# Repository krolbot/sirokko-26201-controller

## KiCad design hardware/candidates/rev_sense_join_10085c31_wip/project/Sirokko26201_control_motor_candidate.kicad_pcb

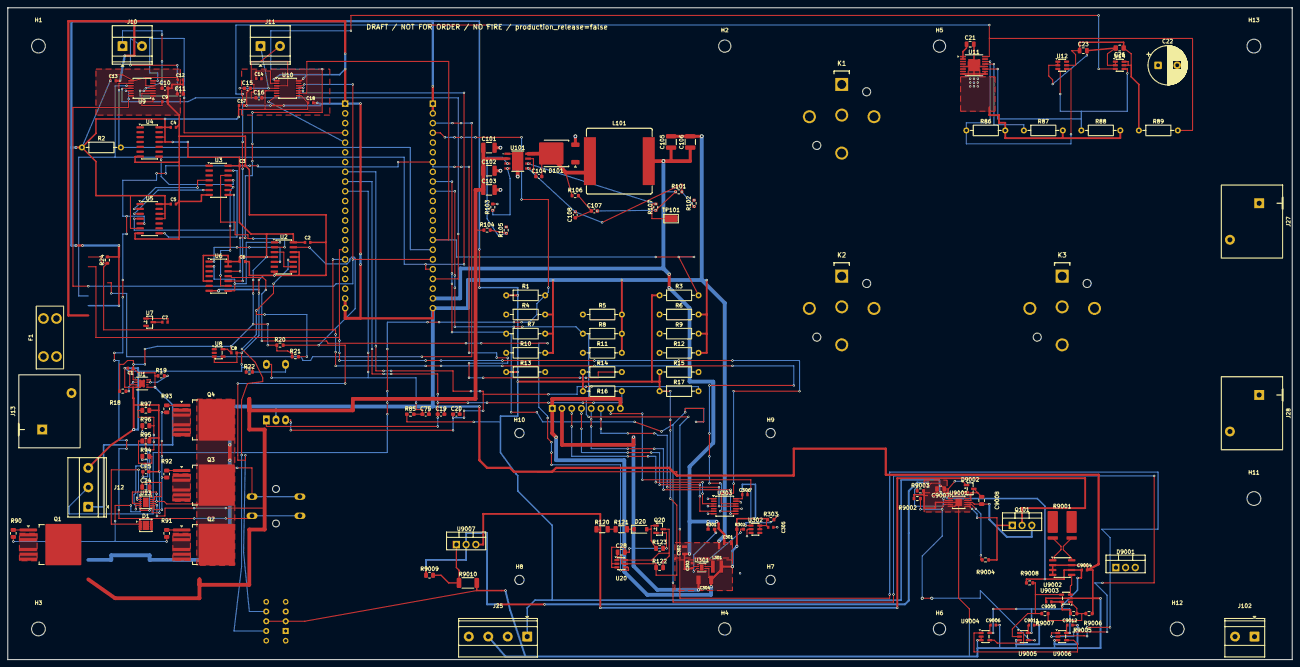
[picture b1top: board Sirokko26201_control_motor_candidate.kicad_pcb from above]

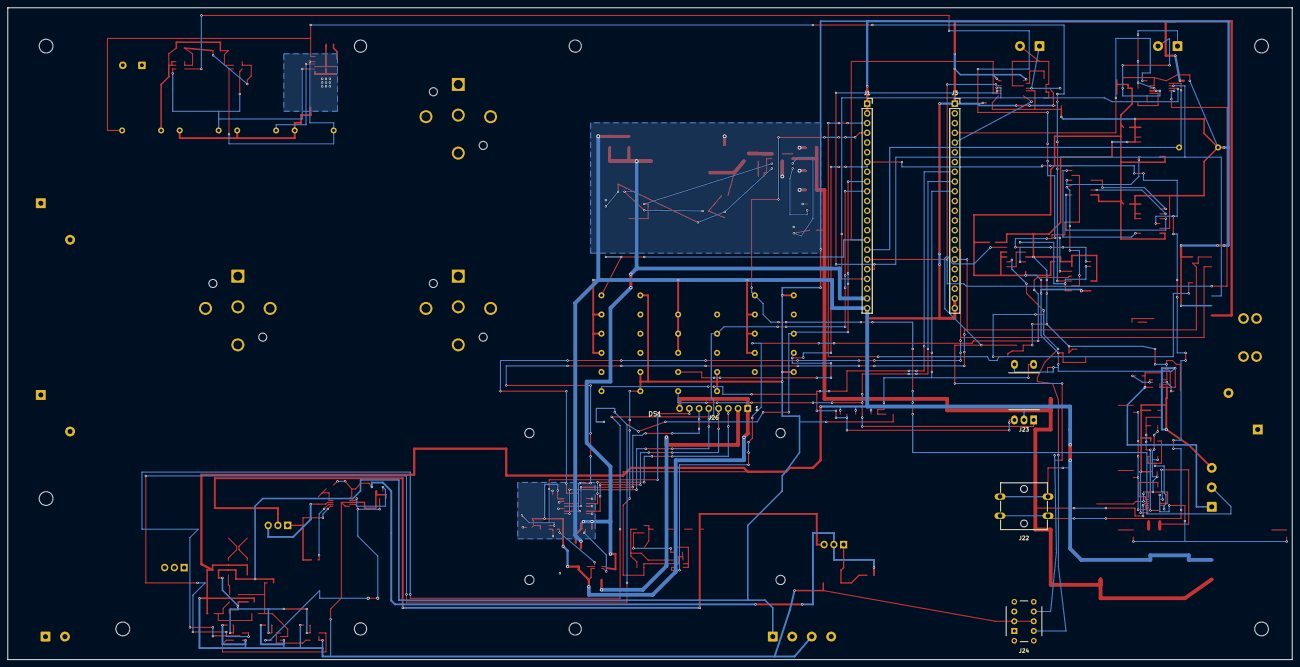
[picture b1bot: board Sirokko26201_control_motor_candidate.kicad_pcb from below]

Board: 2 copper layers, 335.0 x 170.0 mm, 181 parts (7 on the bottom side), 110 nets.

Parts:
C1, C2, C3, C4, C5, C6, C7, C8: 100n 16V X7R; C_Murata_GRM188_1608_Reflow
C9, C14: 0.1uF X7R 16V BIAS; C_Murata_GRM188_1608_Reflow
C10, C15: 0.01uF X7R 16V T+ filter; C_0603_1608Metric
C11, C16: 0.01uF X7R 16V T- filter; C_0603_1608Metric
C12, C17: 0.1uF X7R 16V AVDD; C_Murata_GRM188_1608_Reflow
C13, C18: 0.1uF X7R 16V DVDD; C_Murata_GRM188_1608_Reflow
C19: 10n ENC_A_FILTER; C_0603_1608Metric_Pad1.08x0.95mm_HandSolder
C20: 10n ENC_B_FILTER; C_0603_1608Metric_Pad1.08x0.95mm_HandSolder
C21: 100nF 100V X7R GRM21BR72A104KAC4L VM_BYPASS; C_0805_2012Metric
C22: 330uF 63V EEUFS1J331L BULK_DRAFT; CP_Radial_D10.0mm_P5.00mm
C23: 100nF 50V X7R U12_BYPASS; C_0805_2012Metric
C24: 220nF 100V CVCAP GRM21BR72A224KA01L; C_0805_2012Metric
C25: 100nF 100V CVS GRM188R72A104KA35D; C_0603_1608Metric
C26: 100nF 50V X7R U14_BYPASS; C_0805_2012Metric_Pad1.18x1.45mm_HandSolder
C28: 100nF 100V X7R 10% GRM21BR72A104KAC4L; C_0805_2012Metric
C75: 10n; C_0603_1608Metric_Pad1.08x0.95mm_HandSolder
C101, C102: 2.2uF 100V X7R; C_1210_3225Metric
C103: 22uF 100V BULK; C_1210_3225Metric
C104: 2.2nF 50V X7R; C_0603_1608Metric
C105, C106: 47uF 16V X7R; C_1210_3225Metric
C107: 4.7nF 50V C0G; C_0603_1608Metric
C108: 820pF 50V C0G; C_0603_1608Metric
C301, C302: 10uF GRM21BR61E106KA73L; C_Murata_GRM21B_2012_Reflow
C303: 100nF GRM188R71E104KA01D; C_Murata_GRM188_1608_Reflow
C304: 47uF GRM32ER61C476KE15L; C_Murata_GRM32E_3225_Reflow
C305, C306: 100nF; C_Murata_GRM188_1608_Reflow
C9004, C9005, C9006: 100nF X7R 16V; C_Murata_GRM188_1608_Reflow
C9007: 1uF ±10% X7R 50V 0805; LTC7001 VCC local decoupli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; C_0805_2012Metric
C9008: 1uF ±10% X7R 50V 0805 (BST-TS); C_0805_2012Metric
C9011: 100nF X7R 16V 10%; U9005 local bypass; C_Murata_GRM188_1608_Reflow
C9012: 100nF X7R 16V 10%; U9006 local bypass; C_Murata_GRM188_1608_Reflow
D1: TVS3301DRBR WIP; VSON-8-1EP_3x3mm_P0.65mm_EP1.65x2.4mm
D20: BZT52C15-7-F 15V 500mW; D_SOD-123
D101: STPS5H100B-TR; TO-252-2
D9001: STPS30H100CW; common cathode: K/pin2/tab -> MOTOR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; TO-220-3_Vertical
D9002: MMBD1501A; 200V 200mA silicon low-leakage bootstr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; SOT-23
DS1: Waveshare 18366 / 2.4inch LCD Module; Waveshare_18366_Module_Bside_Envelope_NO_CY
F1: 0997030.WXN / 30A WIP; Keystone_3568_MINI_Blade_3D_ENVELOPE
H1, H3, H11, H12, H13: MountingHole_3.6mm_R5.5_DRAFT
H2, H4: M3; MountingHole_3.2mm_M3
H5, H6: M3 SUPPORT; MountingHole_3.2mm_M3
H7, H8, H9, H10: WAVESHARE18366_M2_DRAFT_NOT_FOR_ORDER; MountingHole_2.4mm_M2_DRAFT
J1: DEVKITC1_J1; PinSocket_1x22_P2.54mm_Vertical
J3: DEVKITC1_J3; PinSocket_1x22_P2.54mm_Vertical
J10: TC_K_EXHAUST_T+_T-; TerminalBlock_Phoenix_MKDS-1,5-2-5.08_1x02_P5.08mm_Horizont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
J11: TC_K_AIR_T+_T-; TerminalBlock_Phoenix_MKDS-1,5-2-5.08_1x02_P5.08mm_Horizont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
J12: ROOM_DS18B20_HARNESS; TerminalBlock_Phoenix_MKDS-1,5-3-5.08_1x03_P5.08mm_Horizont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
J13: 24V_INPUT_PHOENIX_1756993_WIP; Phoenix_1756993_MKDS5HV_2_9.52_ZSZS_3D_ENVELOPE
J22: START_STOP B3F-4055 + B32-1380 RED; SW_SPST_Omron_B3F-40xx
J23: ENCODER EC11E15244G1 + KNOB 41001-1; RotaryEncoder_Alps_EC11E15244G1_Knob41001_3D_ENVELOPE
J24: RESET NKK BB25AB-FA; SW_NKK_BB25AB-FA_3D_ENVELOPE
J25: THERMAL_AND_HW_ENABLE_3V3_ONLY; TerminalBlock_Phoenix_MKDS-1,5-4-5.08_1x04_P5.08mm_Horizont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
J26: TFT CABLE HARWIN M20-9960845 RA THT; Harwin_M20_9960845_1x08_P2.54mm_RA_THT_Bside
J27: GLOW_OUTPUT_PHOENIX_1756993; Phoenix_1756993_MKDS5HV_2_9.52_ZSZS_3D_ENVELOPE
J28: CLUTCH_OUTPUT_PHOENIX_1756993; Phoenix_1756993_MKDS5HV_2_9.52_ZSZS_3D_ENVELOPE
J102: MOTOR_24V_HIGH_SPEED; 125W_HEATER_NAMEPLATE_NOT_M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; TerminalBlock_Phoenix_MKDS-1,5-2-5.08_1x02_P5.08mm_Horizont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
K1: DG85BM-5021-76-1024 + DZ85AB-5-PCB / GLOW; DZ85AB_5_PCB_DG85BM_ENVELOPE
K2: DG85BM-5021-76-1024 + DZ85AB-5-PCB / CLUTCH_RUN; DZ85AB_5_PCB_DG85BM_ENVELOPE
K3: DG85BM-5021-76-1024 + DZ85AB-5-PCB / CLUTCH_SAFE; DZ85AB_5_PCB_DG85BM_ENVELOPE
L101: 33uH Isat>=10A; L_Bourns_SRP1770TA_16.9x16.9mm
L301: 744025003 3.3uH; L_Wuerth_744025003_2828_Reflow
Q1, Q2, Q3, Q4: IPB017N10N5LFATMA1 WIP; Infineon_PG_TO263_7_IPB017N10N5LF
Q20: BC847B,215; SOT-23
Q101: IRFB4110PBF (100V; RDS(on) @ VGS=10V); TO-220-3_Vertical
R1: 4k7; R_Axial_DIN0207_L6.3mm_D2.5mm_P10.16mm_Horizontal
R2, R3, R4, R5, R6, R7, R8, R9, R10, R11, R12, R13, R14, R15: 10k; R_Axial_DIN0207_L6.3mm_D2.5mm_P10.16mm_Horizontal
R16: 2.2k ENC_A_PULLUP; R_Axial_DIN0207_L6.3mm_D2.5mm_P10.16mm_Horizontal
R17: 2.2k ENC_B_PULLUP; R_Axial_DIN0207_L6.3mm_D2.5mm_P10.16mm_Horizontal
R18, R19, R20, R21, R22, R102, R105, R107: 10k 1%; R_0603_1608Metric
R24: 10k TFT_CS_PULLUP; R_0603_1608Metric
R85: 2.2k; R_0603_1608Metric_Pad0.98x0.95mm_HandSolder
R86: 4k7 DRV_IN1_PULLDOWN; R_Axial_DIN0207_L6.3mm_D2.5mm_P10.16mm_Horizontal
R87: 4k7 DRV_IN2_PULLDOWN; R_Axial_DIN0207_L6.3mm_D2.5mm_P10.16mm_Horizontal
R88: 4k7 DRV_IN3_PULLDOWN; R_Axial_DIN0207_L6.3mm_D2.5mm_P10.16mm_Horizontal
R89: 10k RELAY_DRIVER_OK_PULLUP; R_Axial_DIN0207_L6.3mm_D2.5mm_P10.16mm_Horizontal
R90: 4.7R Q1_GATE; R_0805_2012Metric
R91: 4.7R Q2_GATE; R_0805_2012Metric
R92: 4.7R Q3_GATE; R_0805_2012Metric
R93: 4.7R Q4_GATE; R_0805_2012Metric
R94: 84.5k 1% OV_TOP; R_0805_2012Metric
R95: 3.48k 1% OV_BOT; R_0805_2012Metric
R96: 75k 1% EN_TOP; R_0805_2012Metric
R97: 5.62k 1% EN_BOT; R_0805_2012Metric
R101, R103: 31.6k 1%; R_0603_1608Metric
R104: 100k 1%; R_0603_1608Metric
R106: 82k 1%; R_0603_1608Metric
R120, R121: 2.7k 1% 0.25W RC1206FR-072K7L; R_1206_3216Metric
R122: 47k 1% 0.125W RC0805FR-0747KL; R_0805_2012Metric
R123: 100k 1% 0.125W RC0805FR-07100KL; R_0805_2012Metric
R301: 100k 1% EN; R_Yageo_RC0603_1608_Reflow
R302: 100k 1% PG; R_Yageo_RC0603_1608_Reflow
R303: 100k; R_0603_1608Metric
R9001: WSLP27262L000FEA; 2mOhm 1% 5W @70C; WSLP2726
R9002: 100k 1% gate-command pull-down; R_0603_1608Metric
R9003: 130k 1% (VCCUV ≈9.1V rising); R_0603_1608Metric
R9004: 10R gate turn-on damping; R_0603_1608Metric
R9005: 30.1k 1% OCP threshold high; R_0603_1608Metric
R9006: 10.0k 1% OCP threshold low; R_0603_1608Metric
R9007: 1.00M 1% OCP hysteresis feedback; R_0603_1608Metric
R9008: 10k 1% OCP_OK pull-up; R_0603_1608Metric
R9009: 75R 1% 0.125W; LM317 OUT→ADJ; R_0805_2012Metric
R9010: 681R 1% 0.75W; LM317 ADJ→GND; R_2010_5025Metric
TP101: PGOOD_5V_NOT_GPIO; TestPoint_Keystone_5015_Micro_Mini
U1: TPS3431SDRBR; TPS3431_DRB0008A_3D
U2: SN74HCS74D; SOIC-14_3.9x8.7mm_P1.27mm
U3: SN74HCS14D; SOIC-14_3.9x8.7mm_P1.27mm
U4, U5: SN74HCS30D; SOIC-14_3.9x8.7mm_P1.27mm
U6: SN74HCS11D; SOIC-14_3.9x8.7mm_P1.27mm
U7: TPS3839G33DBZR; SOT-23
U8: SN74LVC1G14DBVR; SOT-23-5
U9, U10: MAX31856MUD+; TSSOP-14_4.4x5mm_P0.65mm
U11: DRV8803PWPR; HTSSOP-16-1EP_4.4x5mm_P0.65mm_EP3x3mm
U12, U14, U20: SN74LVC1G97DBVR; SOT-23-6
U13: LM74800QDRRRQ1 WIP_NOT_TRANSIENT_QUALIFIED; WSON-12-1EP_3x3mm_P0.5mm_EP1.5x2.5mm
U101: LM5013DDAR; DDA0008B_LM5013DDAR_TI4214849B_3D
U301: TPS62162DSGR; Texas_DSG0008A_WSON-8-1EP_2x2mm_P0.5mm_EP0.9x1.6mm
U302: TPS3808G33DBVR; SOT-23-6
U303: 74LVC125APW,118 Nexperia ONLY; TSSOP-14_4.4x5mm_P0.65mm
U9001: LTC7001IMSE#PBF; MSOP-10 EP; MSOP-10-1EP_3x3mm_P0.5mm_EP1.68x1.88mm
U9002: INA240A1ID; SOIC-8_3.9x4.9mm_P1.27mm
U9003: TLV9020DBVR; SOT-23-5
U9004: SN74LVC1G32DBVR; SOT-23-5
U9005, U9006: SN74LVC1G08DBVR; SOT-23-5
U9007: LM317HVT/NOPB TO-220; TJ 0…125C; TO-220-3_Vertical

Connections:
+5V_DEVKIT: C105.1, C106.1, C107.2, C301.1, C302.1, C303.1, J1.21, L101.2, R101.1, R107.1, R301.1, U301.2
/+3V3: C1.1, C2.1, C3.1, C4.1, C5.1, C6.1, C7.1, C8.1, C12.1, C13.1, C17.1, C18.1, C23.1, C26.1, C28.1, C9004.1, C9005.1, C9006.1, C9011.1, C9012.1, J1.1, J1.2, J12.1, J25.1, R1.1, R2.1, R3.1, R13.1, R14.1, R15.1, R16.1, R17.1, R18.1, R19.1, R20.1, R21.1, R24.2, R85.1, R89.1, R122.1, R9005.1, R9008.1, U1.1, U1.3, U1.5, U2.4, U2.14, U3.14, U4.11, U4.12, U4.14, U5.6, U5.11, U5.12, U5.14, U6.5, U6.13, U6.14, U7.3, U8.5, U9.5, U9.8, U10.5, U10.8, U12.5, U14.5, U14.6, U20.1, U20.5, U9002.6, U9003.5, U9004.5, U9005.5, U9006.5
/ALLOW_LATCH: U2.5, U6.1
/ARM_READY: J3.7, R10.1, U4.5, U5.1
/CLEAR_OK: U2.1, U6.2, U6.8
/CLEAR_OK_BASE: U3.10, U6.9
/CLUTCH_STAGE1: K2.87, K3.30
/CLUTCH_SWITCHED_POS: J28.1, K3.87
/ENC_A: C19.1, J3.9, J23.1, R16.2
/ENC_B: C20.1, J3.8, J23.3, R17.2
/ENC_SW: C75.1, J3.10, J23.4, R85.2
/EXT_SAFETY_ENABLE: J25.4, U6.6
/FAN_REQUEST: J1.9, R7.1, U9006.1
/FUEL_CMD: J1.8, R5.1, R87.1, U3.3, U11.13
/FUEL_PERMIT: J3.18, R6.1, U3.5, U6.4
/GLOW_CMD: J1.20, R4.1, U3.9, U12.6
/GLOW_ENABLE_HW: R86.1, U11.14, U12.4
/GLOW_SWITCHED_POS: J27.1, K1.87
/GND: C1.2, C2.2, C3.2, C4.2, C5.2, C6.2, C7.2, C8.2, C9.2, C10.2, C11.2, C12.2, C13.2, C14.2, C15.2, C16.2, C17.2, C18.2, C19.2, C20.2, C21.2, C22.2, C23.2, C25.2, C26.2, C28.2, C75.2, C101.2, C102.2, C103.2, C105.2, C106.2, C301.2, C302.2, C303.2, C304.2, C305.2, C306.2, C9004.2, C9005.2, C9006.2, C9007.2, C9011.2, C9012.2, D1.5, D1.6, D1.7, D1.8, D101.3, D9001.1, D9001.3, J1.22, J3.1, J3.21, J3.22, J12.3, J13.2, J22.2, J23.2, J23.5, J24.2, J24.5, J25.3, J26.2, J27.2, J28.2, J102.2, Q20.2, R4.2, R5.2, R6.2, R7.2, R8.2, R9.2, R10.2, R11.2, R12.2, R22.2, R86.2, R87.2, R88.2, R95.2, R97.2, R102.2, R103.2, R105.2, R123.2, R9002.2, R9003.2, R9006.2, R9010.2, U1.4, U1.9, U2.7, U2.11, U2.12, U3.7, U4.7, U5.7, U6.7, U7.1, U8.3, U9.1, U9.14, U10.1, U10.14, U11.5, U11.8, U11.9, U11.10, U11.12, U11.17, U12.1, U12.2, U13.7, U14.1, U14.2, U20.2, U20.3, U101.1, U101.9, U301.1, U301.4, U301.5, U301.9, U302.2, U303.1, U303.4, U303.7, U303.10, U303.13, U9001.3, U9001.5, U9001.11, U9002.2, U9002.3, U9002.4, U9002.7, U9003.2, U9004.2, U9004.3, U9005.3, U9006.3
/HW_RESET_CLK: U2.3, U2.9
/INPUT_PROTECTION_WIP_NOT_QUALIFIED/CAP_NET: C24.1, U13.11
/INPUT_PROTECTION_WIP_NOT_QUALIFIED/DGATE: R90.1, R91.1, U13.1
/INPUT_PROTECTION_WIP_NOT_QUALIFIED/EN_DIV: R96.2, R97.1, U13.6
/INPUT_PROTECTION_WIP_NOT_QUALIFIED/HGATE: R92.1, R93.1, U13.8
/INPUT_PROTECTION_WIP_NOT_QUALIFIED/OV_DIV: R94.2, R95.1, U13.5
/INPUT_PROTECTION_WIP_NOT_QUALIFIED/Q1_GATE: Q1.1, R90.2
/INPUT_PROTECTION_WIP_NOT_QUALIFIED/Q2_GATE: Q2.1, R91.2
/INPUT_PROTECTION_WIP_NOT_QUALIFIED/Q3_GATE: Q3.1, R92.2
/INPUT_PROTECTION_WIP_NOT_QUALIFIED/Q4_GATE: Q4.1, R93.2
/INPUT_PROTECTION_WIP_NOT_QUALIFIED/REV_MID: C24.2, C25.1, Q1.4, Q2.4, Q3.4, Q4.4, R94.1, R96.1, U13.3, U13.4, U13.10, U13.12
/INPUT_PROTECTION_WIP_NOT_QUALIFIED/VIN_FUSED: D1.1, D1.2, D1.3, D1.4, F1.2, Q1.2, Q1.3, Q1.5, Q1.6, Q1.7, Q2.2, Q2.3, Q2.5, Q2.6, Q2.7, U13.2
/K_CLUTCH_RUN_COIL_LOW: K2.85, U11.4
/K_CLUTCH_SAFE_COIL_LOW: K3.85, U11.6
/K_GLOW_COIL_LOW: K1.85, U11.3
/LOGIC_POWER_24_TO_5V__DRAFT_NOT_FOR_ORDER/BOOT: C104.1, U101.7
/LOGIC_POWER_24_TO_5V__DRAFT_NOT_FOR_ORDER/EN_LOGIC: R104.2, R105.1, U101.3
/LOGIC_POWER_24_TO_5V__DRAFT_NOT_FOR_ORDER/FB: C108.2, R101.2, R102.1, U101.5
/LOGIC_POWER_24_TO_5V__DRAFT_NOT_FOR_ORDER/PGOOD_5V: R107.2, TP101.1, U101.6
/LOGIC_POWER_24_TO_5V__DRAFT_NOT_FOR_ORDER/RAMP: C107.1, C108.1, R106.2
/LOGIC_POWER_24_TO_5V__DRAFT_NOT_FOR_ORDER/RON: R103.1, U101.4
/LOGIC_POWER_24_TO_5V__DRAFT_NOT_FOR_ORDER/SW: C104.2, D101.2, L101.1, R106.1, U101.8
/MOTOR_PWM_REBUILD_CANDIDATE/BST: C9008.1, D9002.3, U9001.9
/MOTOR_PWM_REBUILD_CANDIDATE/FAN_REQUEST_OR_EMERG: U9004.4, U9005.1
/MOTOR_PWM_REBUILD_CANDIDATE/FAN_WORK_PWM: U9004.1, U9006.4
/MOTOR_PWM_REBUILD_CANDIDATE/GATE_Q101: Q101.1, R9004.2, U9001.6
/MOTOR_PWM_REBUILD_CANDIDATE/ISENSE_OUT: U9002.5, U9003.3
/MOTOR_PWM_REBUILD_CANDIDATE/MOTOR_GATE_CMD: R9002.1, U9001.4, U9005.4
/MOTOR_PWM_REBUILD_CANDIDATE/MOTOR_POS: D9001.2, J102.1, R9001.2, U9002.1
/MOTOR_PWM_REBUILD_CANDIDATE/OCP_OK: R9007.1, R9008.2, U9003.4, U9005.2
/MOTOR_PWM_REBUILD_CANDIDATE/OCP_THRESH: R9005.2, R9006.1, R9007.2, U9003.1
/MOTOR_PWM_REBUILD_CANDIDATE/SW_SHUNT_HI: C9008.2, Q101.3, R9001.1, U9001.8, U9002.8
/MOTOR_PWM_REBUILD_CANDIDATE/TGUP: R9004.1, U9001.7
/MOTOR_PWM_REBUILD_CANDIDATE/VADJ: R9009.2, R9010.1, U9007.1
/MOTOR_PWM_REBUILD_CANDIDATE/VCCUV: R9003.1, U9001.2
/MOTOR_PWM_REBUILD_CANDIDATE/VDRV12V: C9007.1, D9002.1, R9009.1, U9001.1, U9007.2
/NOT_CLEAR_OK: U3.11, U4.8
/NOT_FUEL_CMD: U3.4, U5.2
/NOT_FUEL_PERMIT: U3.6, U5.3
/NOT_GLOW_CMD: U3.8, U5.4
/NOT_RESET_ACCEPT: U3.13, U5.8
/NOT_SW_TRIP: U3.2, U4.6
/P24_BASE: D20.2, Q20.1, R123.1
/P24_PRESENT: U6.11, U20.4
/P24_PROTECTED: C21.1, C22.1, C101.1, C102.1, C103.1, K1.30, K1.86, K2.30, K2.86, K3.86, Q3.2, Q3.3, Q3.5, Q3.6, Q3.7, Q4.2, Q4.3, Q4.5, Q4.6, Q4.7, Q101.2, R104.1, R120.1, U11.1, U11.2, U13.9, U101.2, U9007.3
/P24_SENSE_N: Q20.3, R122.2, U20.6
/P24_SERIES_MID: R120.2, R121.1
/P24_ZENER_K: D20.1, R121.2
/PG_OK: U4.1, U7.2
/RELAY_DRIVER_OK: R89.2, U6.10, U11.16
/RESET_ACCEPT: U2.2, U3.12
/RESET_HW_NC_N: J24.6, R20.2, U2.13
/RESET_HW_NO_N: J24.4, R21.2, U2.10
/RESET_REQUEST: J1.6, J24.1, R13.2
/ROOM_DQ: J1.4, J12.2, R1.2
/SAFETY_OK: J1.5, R12.1, R88.1, U6.3, U11.11, U12.3, U14.4
/SAFETY_OK_RAW: U6.12, U14.3
/SPEED_CMD: J1.10, R8.1, U9006.2
/START_REQUEST: J1.7, J22.1, R14.2, U5.5
/STOP_OK: U4.3, U8.4
/STOP_STATUS: J1.12, R15.2, U8.2
/SW_TRIP: J3.6, R11.1, U3.1
/TC_AIR_BIAS: C14.1, U10.2
/TC_AIR_CS: J1.15, R3.2, U10.9
/TC_AIR_DRDY: J3.5, U10.7
/TC_AIR_TM: C16.1, J11.2, U10.3
/TC_AIR_TP: C15.1, J11.1, U10.4
/TC_EXH_BIAS: C9.1, U9.2
/TC_EXH_CS: J1.16, R2.2, U9.9
/TC_EXH_DRDY: J3.4, U9.7
/TC_EXH_TM: C11.1, J10.2, U9.3
/TC_EXH_TP: C10.1, J10.1, U9.4
/TC_SCK: J1.18, U9.10, U10.10, U303.5
/TC_SDI_MOSI: J1.17, U9.12, U10.12, U303.2
/TC_SDO_MISO: J1.19, U9.11, U10.11
/TFT_3V3: C304.1, C305.1, C306.1, J26.1, J26.8, L301.2, R302.1, R303.1, U301.6, U302.5, U302.6, U303.14
/TFT_CS: J3.17, R24.1, U303.9
/TFT_CS_BUF: J26.5, U303.8
/TFT_DC: J3.16, U303.12
/TFT_DC_BUF: J26.6, U303.11
/TFT_MOSI_BUF: J26.3, U303.3
/TFT_POWER_3V3_DRAFT/TFT_3V3_PG: R302.2, U301.8
/TFT_POWER_3V3_DRAFT/TFT_PWR_EN: R301.2, U301.3
/TFT_POWER_3V3_DRAFT/TFT_PWR_SW: L301.1, U301.7
/TFT_RESET_N: J26.7, R303.2, U302.1
/TFT_SCK_BUF: J26.4, U303.6
/THERMAL_OK: J25.2, R22.1, U4.4
/VIN_RAW_24: F1.1, J13.1
/WD_CWD_FIXED: R18.2, U1.2
/WD_HEARTBEAT: J1.11, R9.1, U1.6
/WD_OK: R19.2, U1.7, U1.8, U4.2

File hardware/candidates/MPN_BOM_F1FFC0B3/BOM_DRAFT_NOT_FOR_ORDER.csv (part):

"Ref","Value","Footprint","Qty","DNP","MPN","Manufacturer","Datasheet"
"C1","100n 16V X7R","Capacitor_SMD:C_0603_1608Metric","1","","","",""
"C2","100n 16V X7R","Capacitor_SMD:C_0603_1608Metric","1","","","",""
"C3","100n 16V X7R","Capacitor_SMD:C_0603_1608Metric","1","","","",""
"C4","100n 16V X7R","Capacitor_SMD:C_0603_1608Metric","1","","","",""
"C5","100n 16V X7R","Capacitor_SMD:C_0603_1608Metric","1","","","",""
"C6","100n 16V X7R","Capacitor_SMD:C_0603_1608Metric","1","","","",""
"C7","100n 16V X7R","Capacitor_SMD:C_0603_1608Metric","1","","","",""
"C8","100n 16V X7R","Capacitor_SMD:C_0603_1608Metric","1","","","",""
"C9","0.1uF X7R 16V BIAS","Capacitor_SMD:C_0603_1608Metric","1","","","",""
"C10","0.01uF X7R 16V T+ filter","Capacitor_SMD:C_0603_1608Metric","1","","","",""
"C11","0.01uF X7R 16V T- filter","Capacitor_SMD:C_0603_1608Metric","1","","","",""
"C12","0.1uF X7R 16V AVDD","Capacitor_SMD:C_0603_1608Metric","1","","","",""
"C13","0.1uF X7R 16V DVDD","Capacitor_SMD:C_0603_1608Metric","1","","","",""
"C14","0.1uF X7R 16V BIAS","Capacitor_SMD:C_0603_1608Metric","1","","","",""
"C15","0.01uF X7R 16V T+ filter","Capacitor_SMD:C_0603_1608Metric","1","","","",""
"C16","0.01uF X7R 16V T- filter","Capacitor_SMD:C_0603_1608Metric","1","","","",""
"C17","0.1uF X7R 16V AVDD","Capacitor_SMD:C_0603_1608Metric","1","","","",""
"C18","0.1uF X7R 16V DVDD","Capacitor_SMD:C_0603_1608Metric","1","","","",""
"C19","10n ENC_A_FILTER","Capacitor_SMD:C_0603_1608Metric_Pad1.08x0.95mm_HandSolder","1","","","",""
"C20","10n ENC_B_FILTER","Capacitor_SMD:C_0603_1608Metric_Pad1.08x0.95mm_HandSolder","1","","","",""
"C75","10n","Capacitor_SMD:C_0603_1608Metric_Pad1.08x0.95mm_HandSolder","1","","","",""
"C101","2.2uF 100V X7R","Capacitor_SMD:C_1210_3225Metric","1","","GRM32ER72A225KA35L","",""
"C102","2.2uF 100V X7R","Capacitor_SMD:C_1210_3225Metric","1","","GRM32ER72A225KA35L","",""
"C103","22uF 100V BULK","Capacitor_SMD:C_1210_3225Metric","1","","GRM32ER72A226KE20L","",""
"C104","2.2nF 50V X7R","Capacitor_SMD:C_0603_1608Metric","1","","CC0603KRX7R9BB222","",""
"C105","47uF 16V X7R","Capacitor_SMD:C_1210_3225Metric","1","","GRM32ER61C476KE15L","",""
"C106","47uF 16V X7R","Capacitor_SMD:C_1210_3225Metric","1","","GRM32ER61C476KE15L","",""
"C107","4.7nF 50V C0G","Capacitor_SMD:C_0603_1608Metric","1","","GRM1885C1H472JA01D","",""
"C108","820pF 50V C0G","Capacitor_SMD:C_0603_1608Metric","1","","CC0603JRNPO9BN821","",""
"C301","10uF GRM21BR61E106KA73L","Sirokko_TFT_Passives:C_Murata_GRM21B_2012_Reflow","1","","","",""
"C302","10uF GRM21BR61E106KA73L","Sirokko_TFT_Passives:C_Murata_GRM21B_2012_Reflow","1","","","",""
"C303","100nF GRM188R71E104KA01D","Sirokko_TFT_Passives:C_Murata_GRM188_1608_Reflow","1","","","",""
"C304","47uF GRM32ER61C476KE15L","Sirokko_TFT_Passives:C_Murata_GRM32E_3225_Reflow","1","","","",""
"C305","100nF","Capacitor_SMD:C_0603_1608Metric","1","","","",""
"C306","100nF","Capacitor_SMD:C_0603_1608Metric","1","","","",""
"C9004","100nF X7R 16V","Capacitor_SMD:C_0603_1608Metric","1","","","",""
"C9005","100nF X7R 16V","Capacitor_SMD:C_0603_1608Metric","1","","","",""
"C9006","100nF X7R 16V","Capacitor_SMD:C_0603_1608Metric","1","","","",""
"C9007","1uF ±10% X7R 50V 0805; LTC7001 VCC local decoupling","Capacitor_SMD:C_0805_2012Metric","1","","GRM21BR71H105KA12L","",""
"C9008","1uF ±10% X7R 50V 0805 (BST-TS)","Capacitor_SMD:C_0805_2012Metric","1","","GRM21BR71H105KA12L","",""
"C9011","100nF X7R 16V 10%; U9005 local bypass","Capacitor_SMD:C_0603_1608Metric","1","","","",""
"C9012","100nF X7R 16V 10%; U9006 local bypass","Capacitor_SMD:C_0603_1608Metric","1","","","",""
"D101","STPS5H100B-TR","","1","","STPS5H100B-TR","",""
"D9001","STPS30H100CW; common cathode: K/pin2/tab -> MOTOR_POS; A1/pin1 + A2/pin3 -> GND","Package_TO_SOT_THT:TO-220-3_Vertical","1","","STPS30H100CW","","https://www.st.com/resource/en/datasheet/stps30h100c.pdf"
"D9002","MMBD1501A; 200V 200mA silicon low-leakage bootstrap diode","Package_TO_SOT_SMD:SOT-23","1","","MMBD1501A","ON Semiconductor / Fairchild",""
"J1","DEVKITC1_J1","Connector_PinSocket_2.54mm:PinSocket_1x22_P2.54mm_Vertical","1","","","",""
"J3","DEVKITC1_J3","Connector_PinSocket_2.54mm:PinSocket_1x22_P2.54mm_Vertical","1","","","",""
"J10","TC_K_EXHAUST_T+_T-","TerminalBlock_Phoenix:TerminalBlock_Phoenix_MKDS-1,5-2-5.08_1x02_P5.08mm_Horizontal","1","","","",""
"J11","TC_K_AIR_T+_T-","TerminalBlock_Phoenix:TerminalBlock_Phoenix_MKDS-1,5-2-5.08_1x02_P5.08mm_Horizontal","1","","","",""
"J12","ROOM_DS18B20_HARNESS","TerminalBlock_Phoenix:TerminalBlock_Phoenix_MKDS-1,5-3-5.08_1x03_P5.08mm_Horizontal","1","","1715734","Phoenix Contact","https://static.chipdip.ru/lib/723/DOC011723280.pdf"
"J13","24V_LOGIC_INPUT_ONLY__DRAFT_NOT_FOR_ORDER","TerminalBlock_Phoenix:TerminalBlock_Phoenix_MKDS-1,5-2-5.08_1x02_P5.08mm_Horizontal","1","","1715721","Phoenix Contact","https://static.chipdip.ru/lib/509/DOC040509545.pdf"
"J22","START_STOP B3F-4055 + B32-1380 RED","Button_Switch_THT:SW_SPST_Omron_B3F-40xx","1","","","",""
"J23","ENCODER EC11E15244G1","Sirokko_Panel:RotaryEncoder_Alps_EC11E15244G1","1","","","",""
"J24","RESET NKK BB25AB-FA","Sirokko_Panel:SW_NKK_BB25AB-FA","1","","","",""
"J25","THERMAL_AND_HW_ENABLE_3V3_ONLY","TerminalBlock_Phoenix:TerminalBlock_Phoenix_MKDS-1,5-4-5.08_1x04_P5.08mm_Horizontal","1","","","",""
"J26","TFT_WAVESHARE_18366_CABLE_8P","Sirokko_Connectors:Connfly_DS1021_1x08_P2.54mm_Type1_Drill1.02","1","","DS1021-1*8SF11-B","Connfly",""
"J27","GLOW_OUTPUT_PHOENIX_1756993__POWER_PATH_NOT_CONNECTED","Sirokko_Power:Phoenix_1756993_MKDS5HV_2_9.52_ZSZS","1","","1756993","",""
"J28","CLUTCH_OUTPUT_PHOENIX_1756993__POWER_PATH_NOT_CONNECTED","Sirokko_Power:Phoenix_1756993_MKDS5HV_2_9.52_ZSZS","1","","1756993","",""
"J102","MOTOR_24V_HIGH_SPEED; 125W_HEATER_NAMEPLATE_NOT_MOTOR_RATING","TerminalBlock_Phoenix:TerminalBlock_Phoenix_MKDS-1,5-2-5.08_1x02_P5.08mm_Horizontal","1","","","",""
"L101","33uH Isat>=10A","Inductor_SMD:L_Bourns_SRP1770TA_16.9x16.9mm","1","","SRP1770TA-330M","",""
"L301","744025003 3.3uH","Sirokko_TFT_Passives:L_Wuerth_744025003_2828_Reflow","1","","","",""
"Q101","IRFB4110PBF (100V; RDS(on) @ VGS=10V)","Package_TO_SOT_THT:TO-220-3_Vertical","1","","","",""
"R1","4k7","Resistor_THT:R_Axial_DIN0207_L6.3mm_D2.5mm_P10.16mm_Horizontal","1","","","",""
"R2","10k","Resistor_THT:R_Axial_DIN0207_L6.3mm_D2.5mm_P10.16mm_Horizontal","1","","","",""
"R3","10k","Resistor_THT:R_Axial_DIN0207_L6.3mm_D2.5mm_P10.16mm_Horizontal","1","","","",""
"R4","10k","Resistor_THT:R_Axial_DIN0207_L6.3mm_D2.5mm_P10.16mm_Horizontal","1","","","",""
"R5","10k","Resistor_THT:R_Axial_DIN0207_L6.3mm_D2.5mm_P10.16mm_Horizontal","1","","","",""
"R6","10k","Resistor_THT:R_Axial_DIN0207_L6.3mm_D2.5mm_P10.16mm_Horizontal","1","","","",""
"R7","10k","Resistor_THT:R_Axial_DIN0207_L6.3mm_D2.5mm_P10.16mm_Horizontal","1","","","",""
"R8","10k","Resistor_THT:R_Axial_DIN0207_L6.3mm_D2.5mm_P10.16mm_Horizontal","1","","","",""
"R9","10k","Resistor_THT:R_Axial_DIN0207_L6.3mm_D2.5mm_P10.16mm_Horizontal","1","","","",""
"R10","10k","Resistor_THT:R_Axial_DIN0207_L6.3mm_D2.5mm_P10.16mm_Horizontal","1","","","",""
"R11","10k","Resistor_THT:R_Axial_DIN0207_L6.3mm_D2.5mm_P10.16mm_Horizontal","1","","","",""
"R12","10k","Resistor_THT:R_Axial_DIN0207_L6.3mm_D2.5mm_P10.16mm_Horizontal","1","","","",""
"R13","10k","Resistor_THT:R_Axial_DIN0207_L6.3mm_D2.5mm_P10.16mm_Horizontal","1","","","",""
"R14","10k","Resistor_THT:R_Axial_DIN0207_L6.3mm_D2.5mm_P10.16mm_Horizontal","1","","","",""
"R15","10k","Resistor_THT:R_Axial_DIN0207_L6.3mm_D2.5mm_P10.16mm_Horizontal","1","","","",""
"R16","2.2k ENC_A_PULLUP","Resistor_THT:R_Axial_DIN0207_L6.3mm_D2.5mm_P10.16mm_Horizontal","1","","","",""
"R17","2.2k ENC_B_PULLUP","Resistor_THT:R_Axial_DIN0207_L6.3mm_D2.5mm_P10.16mm_Horizontal","1","","","",""
"R18","10k 1%","Resistor_SMD:R_0603_1608Metric","1","","","",""
"R19","10k 1%","Resistor_SMD:R_0603_1608Metric","1","","","",""
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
